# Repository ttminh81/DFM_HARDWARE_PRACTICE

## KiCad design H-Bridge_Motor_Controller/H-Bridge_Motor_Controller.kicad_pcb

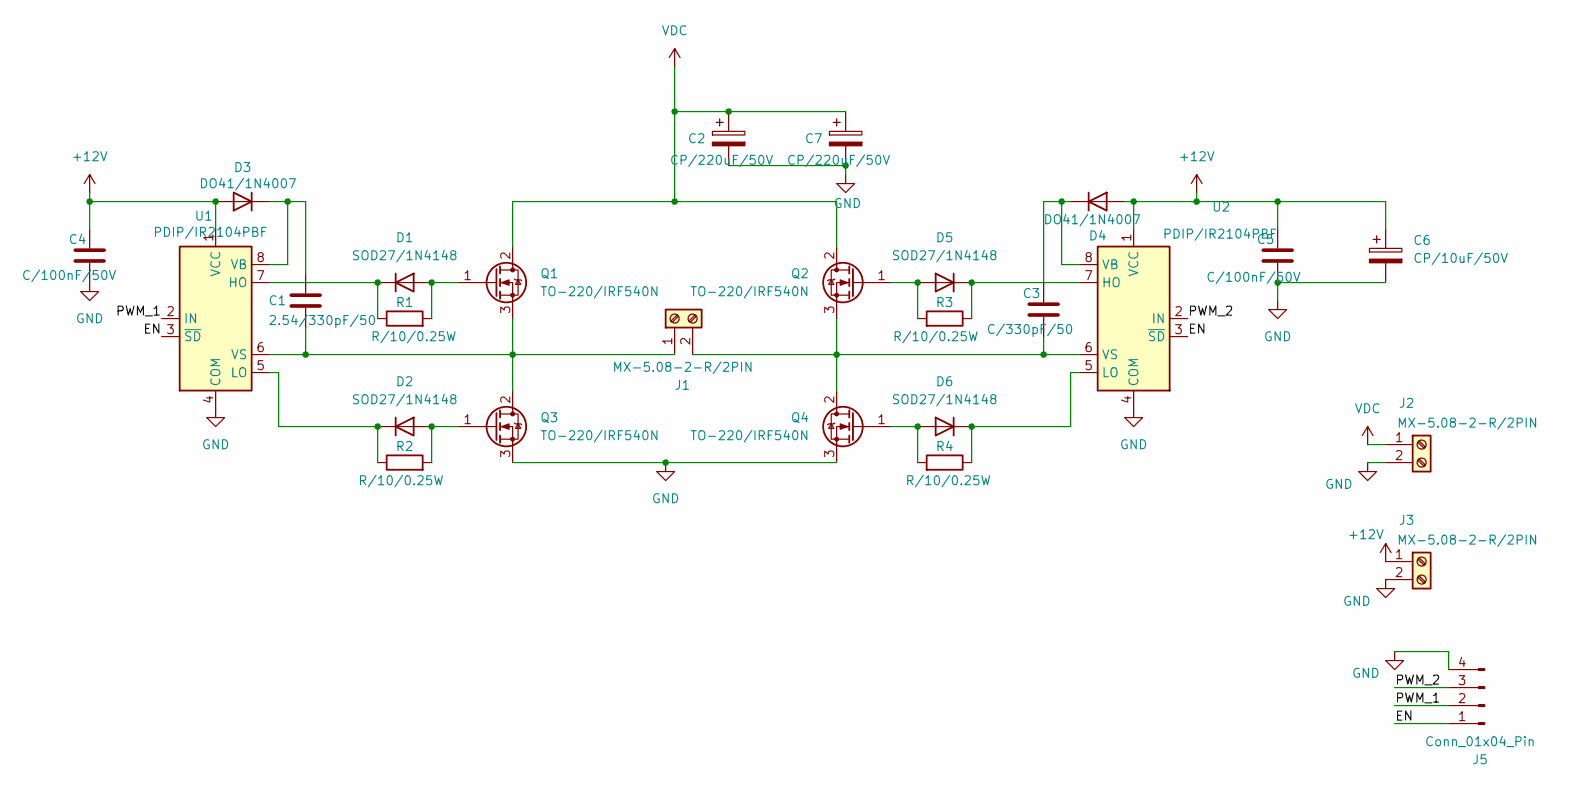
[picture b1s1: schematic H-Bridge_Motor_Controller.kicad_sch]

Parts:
C1: 2.54/330pF/50; C_Disc_D3.4mm_W2.1mm_P2.50mm
C2, C7: CP/220uF/50V; CP_Radial_D10.0mm_P5.00mm
C3: C/330pF/50; C_Disc_D3.4mm_W2.1mm_P2.50mm
C4, C5: C/100nF/50V; C_Disc_D3.4mm_W2.1mm_P2.50mm
C6: CP/10uF/50V; CP_Radial_D5.0mm_P2.00mm
D1, D2, D5, D6: SOD27/1N4148; D_DO-35_SOD27_P7.62mm_Horizontal
D3, D4: DO41/1N4007; D_DO-201AE_P5.08mm_Vertical_AnodeUp
J1, J2, J3: MX-5.08-2-R/2PIN; PhoenixContact_MSTBA_2,5_2-G-5,08_1x02_P5.08mm_Horizontal
J5: Conn_01x04_Pin; PinHeader_1x04_P2.54mm_Vertical
Q1, Q2, Q3, Q4: TO-220/IRF540N; TO-220-3_Vertical_Heatsink
R1, R2, R3, R4: R/10/0.25W; R_Axial_DIN0204_L3.6mm_D1.6mm_P2.54mm_Vertical
U1, U2: PDIP/IR2104PBF; DIP-8_W7.62mm

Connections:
+12V: C4.1, C5.1, C6.1, D3.2 (A), D4.2 (A), J3.1, U1.1 (VCC), U2.1 (VCC)
/EN: J5.1, U1.3 (~SD), U2.3 (~SD)
/PWM_1: J5.2, U1.2 (IN)
/PWM_2: J5.3, U2.2 (IN)
GND: C2.2, C4.2, C5.2, C6.2, C7.2, J2.2, J3.2, J5.4, Q3.3 (S), Q4.3 (S), U1.4 (COM), U2.4 (COM)
unnamed: D1.2 (A), Q1.1 (G), R1.2
unnamed: D1.1 (K), R1.1, U1.7 (HO)
unnamed: D2.2 (A), Q3.1 (G), R2.2
unnamed: D2.1 (K), R2.1, U1.5 (LO)
unnamed: C1.1, D3.1 (K), U1.8 (VB)
unnamed: C3.1, D4.1 (K), U2.8 (VB)
unnamed: D5.2 (A), Q2.1 (G), R3.2
unnamed: D5.1 (K), R3.1, U2.7 (HO)
unnamed: D6.2 (A), Q4.1 (G), R4.2
unnamed: D6.1 (K), R4.1, U2.5 (LO)
unnamed: C1.2, J1.1, Q1.3 (S), Q3.2 (D), U1.6 (VS)
unnamed: C3.2, J1.2, Q2.3 (S), Q4.2 (D), U2.6 (VS)
VDC: C2.1, C7.1, J2.1, Q1.2 (D), Q2.2 (D)

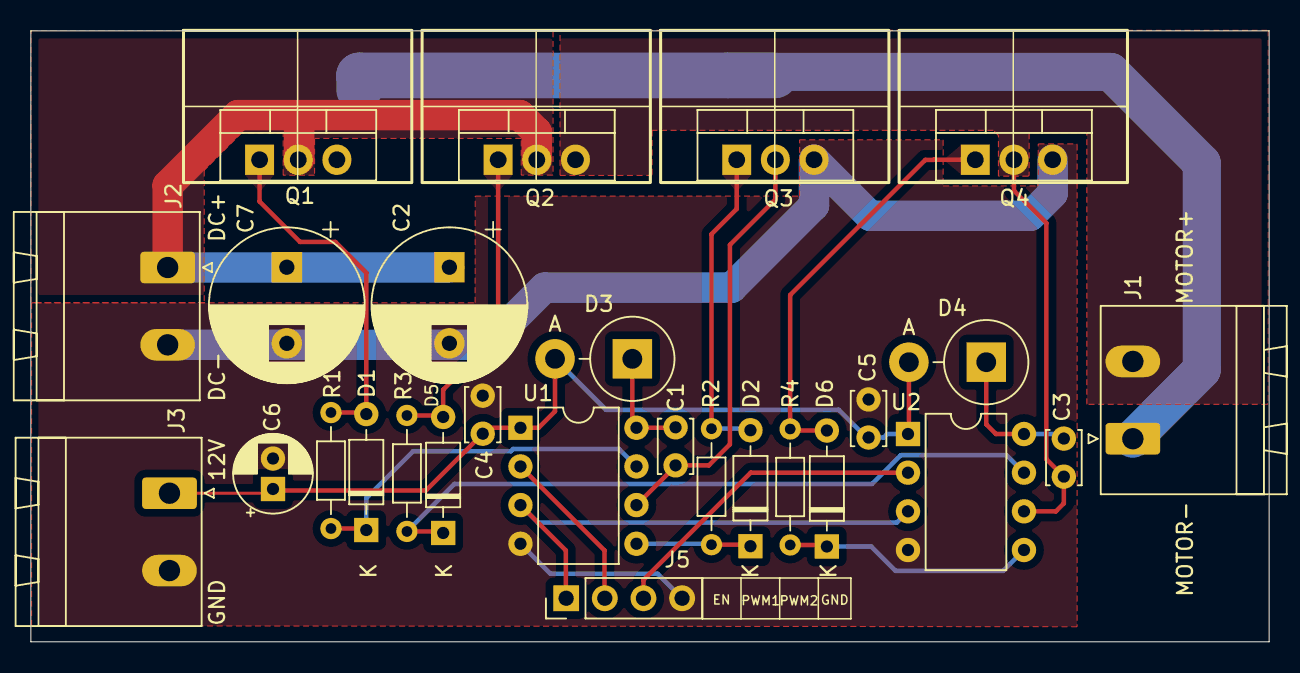
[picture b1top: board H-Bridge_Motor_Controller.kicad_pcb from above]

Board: 2 copper layers, 81.4 x 40.1 mm, 27 parts (0 on the bottom side), 18 nets.
